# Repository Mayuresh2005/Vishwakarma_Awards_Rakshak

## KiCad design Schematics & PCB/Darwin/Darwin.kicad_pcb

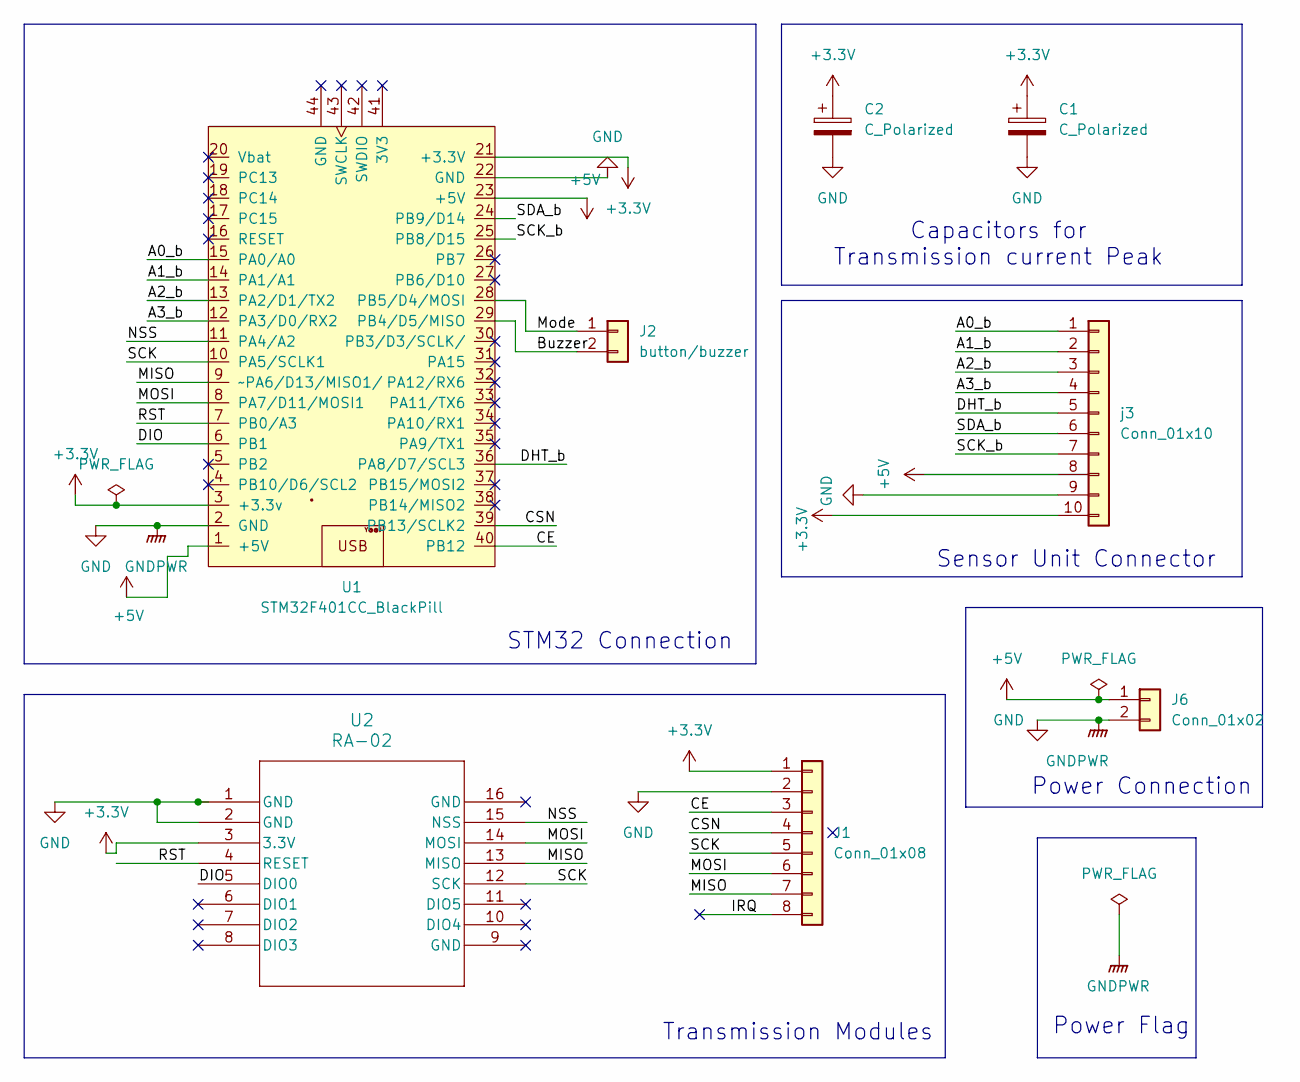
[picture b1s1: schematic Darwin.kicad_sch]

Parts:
C1: C_Polarized; CP_Radial_D8.0mm_P2.50mm
C2: C_Polarized; CP_Radial_D5.0mm_P2.50mm
J1: Conn_01x08; PinHeader_1x08_P2.54mm_Vertical
J2: button/buzzer; PinSocket_1x02_P2.54mm_Vertical
J6: Conn_01x02; PinHeader_1x02_P2.54mm_Vertical
U1: STM32F401CC_BlackPill; STM32F401CCU6
U2: RA-02; RA-02_AIT
j3: Conn_01x10; PinHeader_1x10_P2.54mm_Vertical

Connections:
+3.3V: C1.1, C2.1, J1.1, U1.3 (+3.3v), U1.21 (+3.3V), U2.3 (3.3V), j3.10
+5V: J6.1, U1.1 (+5V), U1.23 (+5V), j3.8
/A0_b: U1.15 (PA0/A0), j3.1
/A1_b: U1.14 (PA1/A1), j3.2
/A2_b: U1.13 (PA2/D1/TX2), j3.3
/A3_b: U1.12 (PA3/D0/RX2), j3.4
/Buzzer: J2.2, U1.29 (PB4/D5/MISO)
/CE: J1.3, U1.40 (PB12)
/CSN: J1.4, U1.39 (PB13/SCLK2)
/DHT_b: U1.36 (PA8/D7/SCL3), j3.5
/DIO: U1.6 (PB1), U2.5 (DIO0)
/IRQ: J1.8
/MISO: J1.7, U1.9 (~PA6/D13/MISO1/), U2.13 (MISO)
/MOSI: J1.6, U1.8 (PA7/D11/MOSI1), U2.14 (MOSI)
/Mode: J2.1, U1.28 (PB5/D4/MOSI)
/NSS: U1.11 (PA4/A2), U2.15 (NSS)
/RST: U1.7 (PB0/A3), U2.4 (RESET)
/SCK: J1.5, U1.10 (PA5/SCLK1), U2.12 (SCK)
/SCK_b: U1.25 (PB8/D15), j3.7
/SDA_b: U1.24 (PB9/D14), j3.6
GND: C1.2, C2.2, J1.2, J6.2, U1.2 (GND), U1.22 (GND), U2.1 (GND), U2.2 (GND), j3.9

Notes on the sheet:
Power Flag
STM32 Connection
Transmission Modules
Power Connection
Capacitors for Transmission current Peak
Sensor Unit Connector

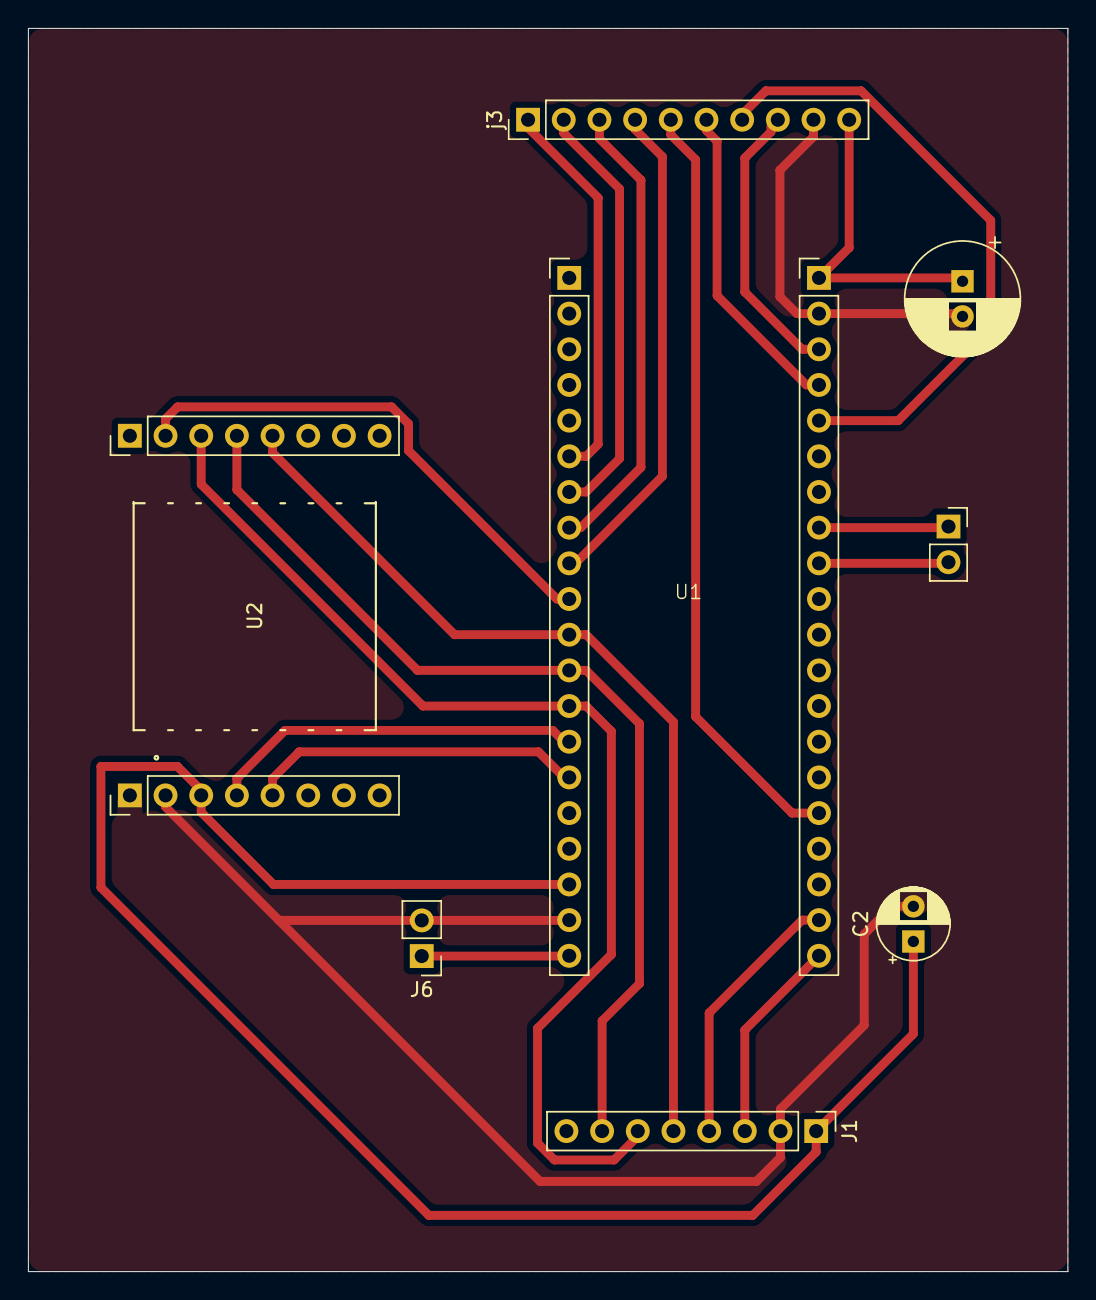
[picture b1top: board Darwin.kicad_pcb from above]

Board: 2 copper layers, 74.0 x 88.5 mm, 8 parts (0 on the bottom side), 20 nets.

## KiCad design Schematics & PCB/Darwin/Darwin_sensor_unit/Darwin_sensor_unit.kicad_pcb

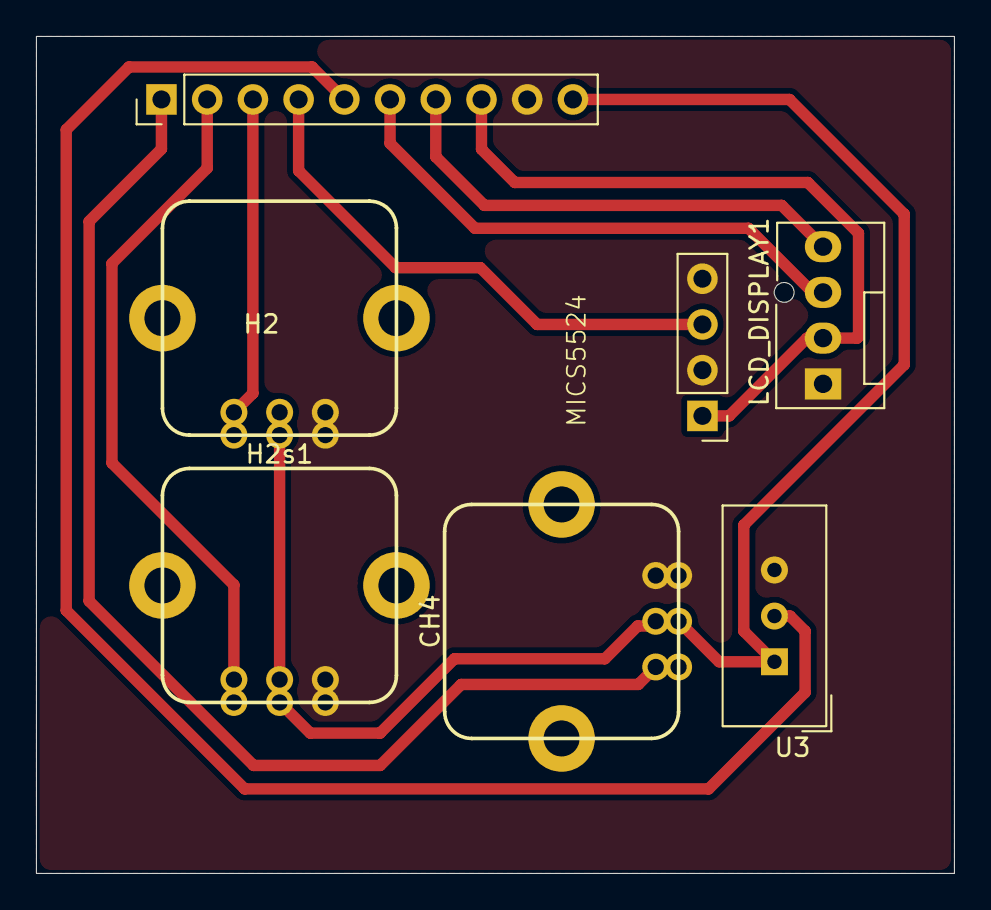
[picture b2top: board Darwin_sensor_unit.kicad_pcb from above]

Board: 2 copper layers, 51.0 x 46.5 mm, 7 parts (0 on the bottom side), 10 nets.

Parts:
CH4: Conn_01x03; SEN0570-DIP
H2, H2s1: Conn_01x03; SEN0570-DIP
LCD_DISPLAY1: Conn_01x04; FanPinHeader_1x04_P2.54mm_Vertical
MICS5524: Conn_01x04; MICS_5524_DFrobot_gas_sensor
Top_conn1: Conn_01x10; PinHeader_1x10_P2.54mm_Vertical
U3: DHT11; Aosong_DHT11_5.5x12.0_P2.54mm_3pin

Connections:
+3.3V: CH4.2, H2.2, H2s1.2, Top_conn1.10, U3.1 (VCC)
+5V: LCD_DISPLAY1.2, MICS5524.1, Top_conn1.8
/A0: CH4.3, Top_conn1.1
/A1: H2s1.3, Top_conn1.2
/A2: H2.3, Top_conn1.3
/A3: MICS5524.3, Top_conn1.4
/DHT: Top_conn1.5, U3.2 (IO)
/SCK: LCD_DISPLAY1.4, Top_conn1.7
/SDA: LCD_DISPLAY1.3, Top_conn1.6
GND: CH4.1, H2.1, H2s1.1, LCD_DISPLAY1.1, MICS5524.2, MICS5524.4, Top_conn1.9, U3.4 (GND)

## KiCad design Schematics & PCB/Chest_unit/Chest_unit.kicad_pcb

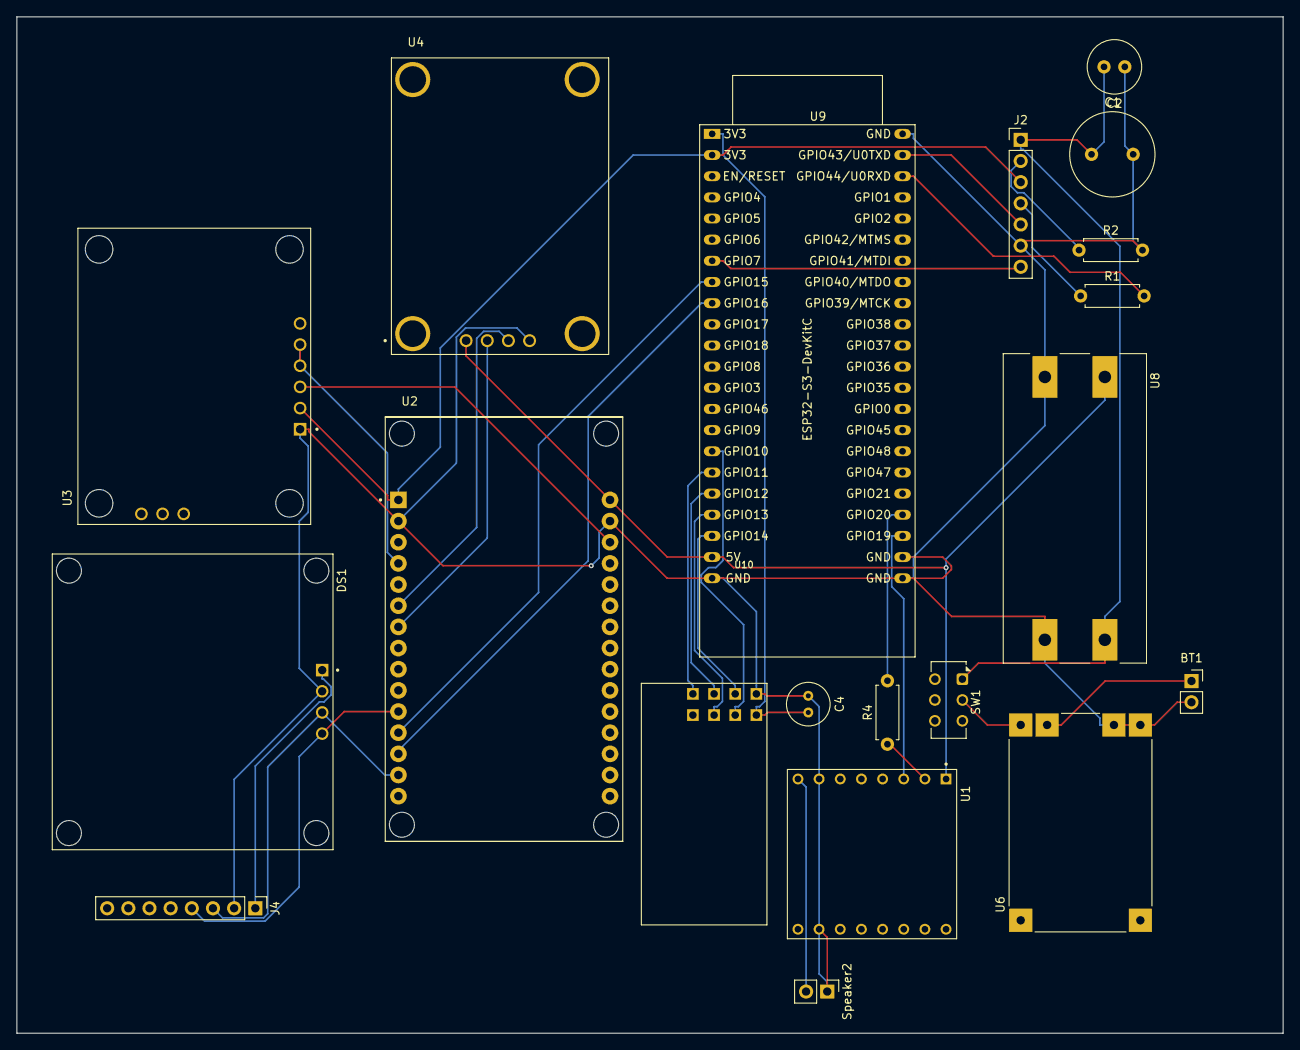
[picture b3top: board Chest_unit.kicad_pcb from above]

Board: 2 copper layers, 152.0 x 122.0 mm, 20 parts (0 on the bottom side), 29 nets.

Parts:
BT1: 1S LiPo 3000mAh+; PinSocket_1x02_P2.54mm_Vertical
C1: 1000uF; C_Radial_D10.0mm_H12.5mm_P5.00mm
C2: 100uF; C_Radial_D6.3mm_H5.0mm_P2.50mm
C4: 10uF; C_Radial_D5.0mm_H5.0mm_P2.00mm
DS1: OLED_128X64_1.3_I2C; LCD_OLED_128X64_1.3_I2C
J2: SIM800L; PinHeader_1x07_P2.54mm_Vertical
J4: MPU6050; PinHeader_1x08_P2.54mm_Vertical
R1, R4: 1k; R_Axial_DIN0207_L6.3mm_D2.5mm_P7.62mm_Horizontal
R2: 4.7k; R_Axial_DIN0207_L6.3mm_D2.5mm_P7.62mm_Horizontal
SW1: SW_DPDT_x2; SW_CK_JS202011CQN_DPDT_Straight
Speaker2: 3 W 4-8 Ω; PinHeader_1x02_P2.54mm_Vertical
U1: DFR0299; MODULE_DFR0299
U2: ESP32-DEVKIT-V1; MODULE_ESP32_DEVKIT_V1
U3: AD8232; MODULE_SEN-12650
U4: NEO-6M GPS; XCVR_ZC323200
U6: TP4056_MICRO-USB_CHARGER_-_1A; MODULE_TP4056_MICRO-USB_CHARGER_-_1A
U8: MT3608_BOOSTER_MODULE; MODULE_MT3608_DC-DC_STEP_UP_CONVERTER_2A_BOOSTER_MODULE
U9: ESP32-S3-DevKitC
U10: NRF24L01_; NRF24L01-PCB-AERIAL

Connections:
+3V3: C4.2, J2.3, U2.1 (3V3), U3.JP3_2 (3.3V), U9.1 (3V3), U9.2 (3V3), U10.P$2 (VCC)
+5V: U1.1 (VCC), U2.30 (VIN), U4.1 (VCC), U8.VOUT_P (VOUT+), U9.21 (5V)
/D2: U2.4 (D2), U3.JP3_4 (LO-), U3.JP3_5 (LO+)
/D13: U2.28 (D13), U3.JP3_3 (SIGNAL_OUT)
/GPIO7: J2.7, U9.7 (GPIO7/ADC1_CH6)
/GPIO10: U9.16 (GPIO10/ADC1_CH9), U10.P$4 (CSN)
/GPIO11: U9.17 (GPIO11/ADC2_CH0), U10.P$7 (MISO)
/GPIO12: U9.18 (GPIO12/ADC2_CH1), U10.P$5 (SCK)
/GPIO13: U9.19 (GPIO13/ADC2_CH2), U10.P$6 (MOSI)
/GPIO14: U9.20 (GPIO14/ADC2_CH3), U10.P$3 (CE)
/GPIO15: U2.13 (TX0), U9.9 (GPIO16/ADC2_CH5/32K_N)
/GPIO16: U2.12 (RX0), U9.8 (GPIO15/ADC2_CH4/32K_P)
/GPIO19: U1.3 (TX), U9.25 (GPIO19/USB_D-)
/GPIO20: R4.2, U9.26 (GPIO20/USB_D+)
/RX: J2.5, U9.43 (GPIO43/U0TXD)
/RX2: U2.6 (RX2), U4.3 (TX)
/Rx_S3: R1.2, U9.42 (GPIO44/U0RXD)
/SCL: DS1.3 (SCK), J4.3, U2.14 (D22)
/SDA: DS1.4 (SDA), J4.4, U2.11 (D21)
/TX: J2.4, R1.1
/TX2: U2.7 (TX2), U4.2 (RX)
/V: DS1.1 (VDD), J4.1
/VIN: C1.1, C2.2, J2.1, SW1.1 (A), U8.VIN_P (VIN+)
GND: BT1.2 (-), C1.2, C2.1, C4.1, DS1.2 (GND), J2.6, J4.2, R2.2, Speaker2.1, U1.7 (GND), U1.10 (GND), U2.2 (GND), U2.29 (GND), U3.JP3_1 (GND), U4.4 (GND), U6.BAT_N (BAT-), U6.OUT_N (OUT-), U8.VIN_N (VIN-), U8.VOUT_N (VOUT-), U9.22 (GND), U9.23 (GND), U9.24 (GND), U9.44 (GND), U10.P$1 (GND)
unnamed: BT1.1 (+), U6.BAT_P (BAT+)
unnamed: J2.2, R2.1
unnamed: SW1.2 (B), U6.OUT_P (OUT+)
unnamed: R4.1, U1.2 (RX)
unnamed: Speaker2.2, U1.8 (SPK2)
